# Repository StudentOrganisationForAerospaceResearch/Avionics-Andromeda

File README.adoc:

= Andromeda Sensor Development Board

Andromeda is the development board for SOAR's 2018 competition avionics system.

Hardware Designs are incremented by version.
For example; *AndromedaV1* is version 1.

The design files for each version are available along with pdf schematics,
assembly drawings and gerber files.

Each hardware version contains the following design files
----

* ___VX.pro - Kicad project
* ___VX.sch - Kicad main schematic
* ___VX.kicad_pcb - Kicad PCB design
* ___.sch - several hierarchical schematic
* ___V.net - Kicad netlist file
* ___VX-cache.dcm - Kicad component description cache
* ___VX-cache.lib - Kicad component library cache
* ___VX-Schematic.pdf - PDF Schematic
* ___VX-AssemblyDrawing.pdf PDF export of fabrication layer
* Gerbers - Gerber files exported with protel extensions
----

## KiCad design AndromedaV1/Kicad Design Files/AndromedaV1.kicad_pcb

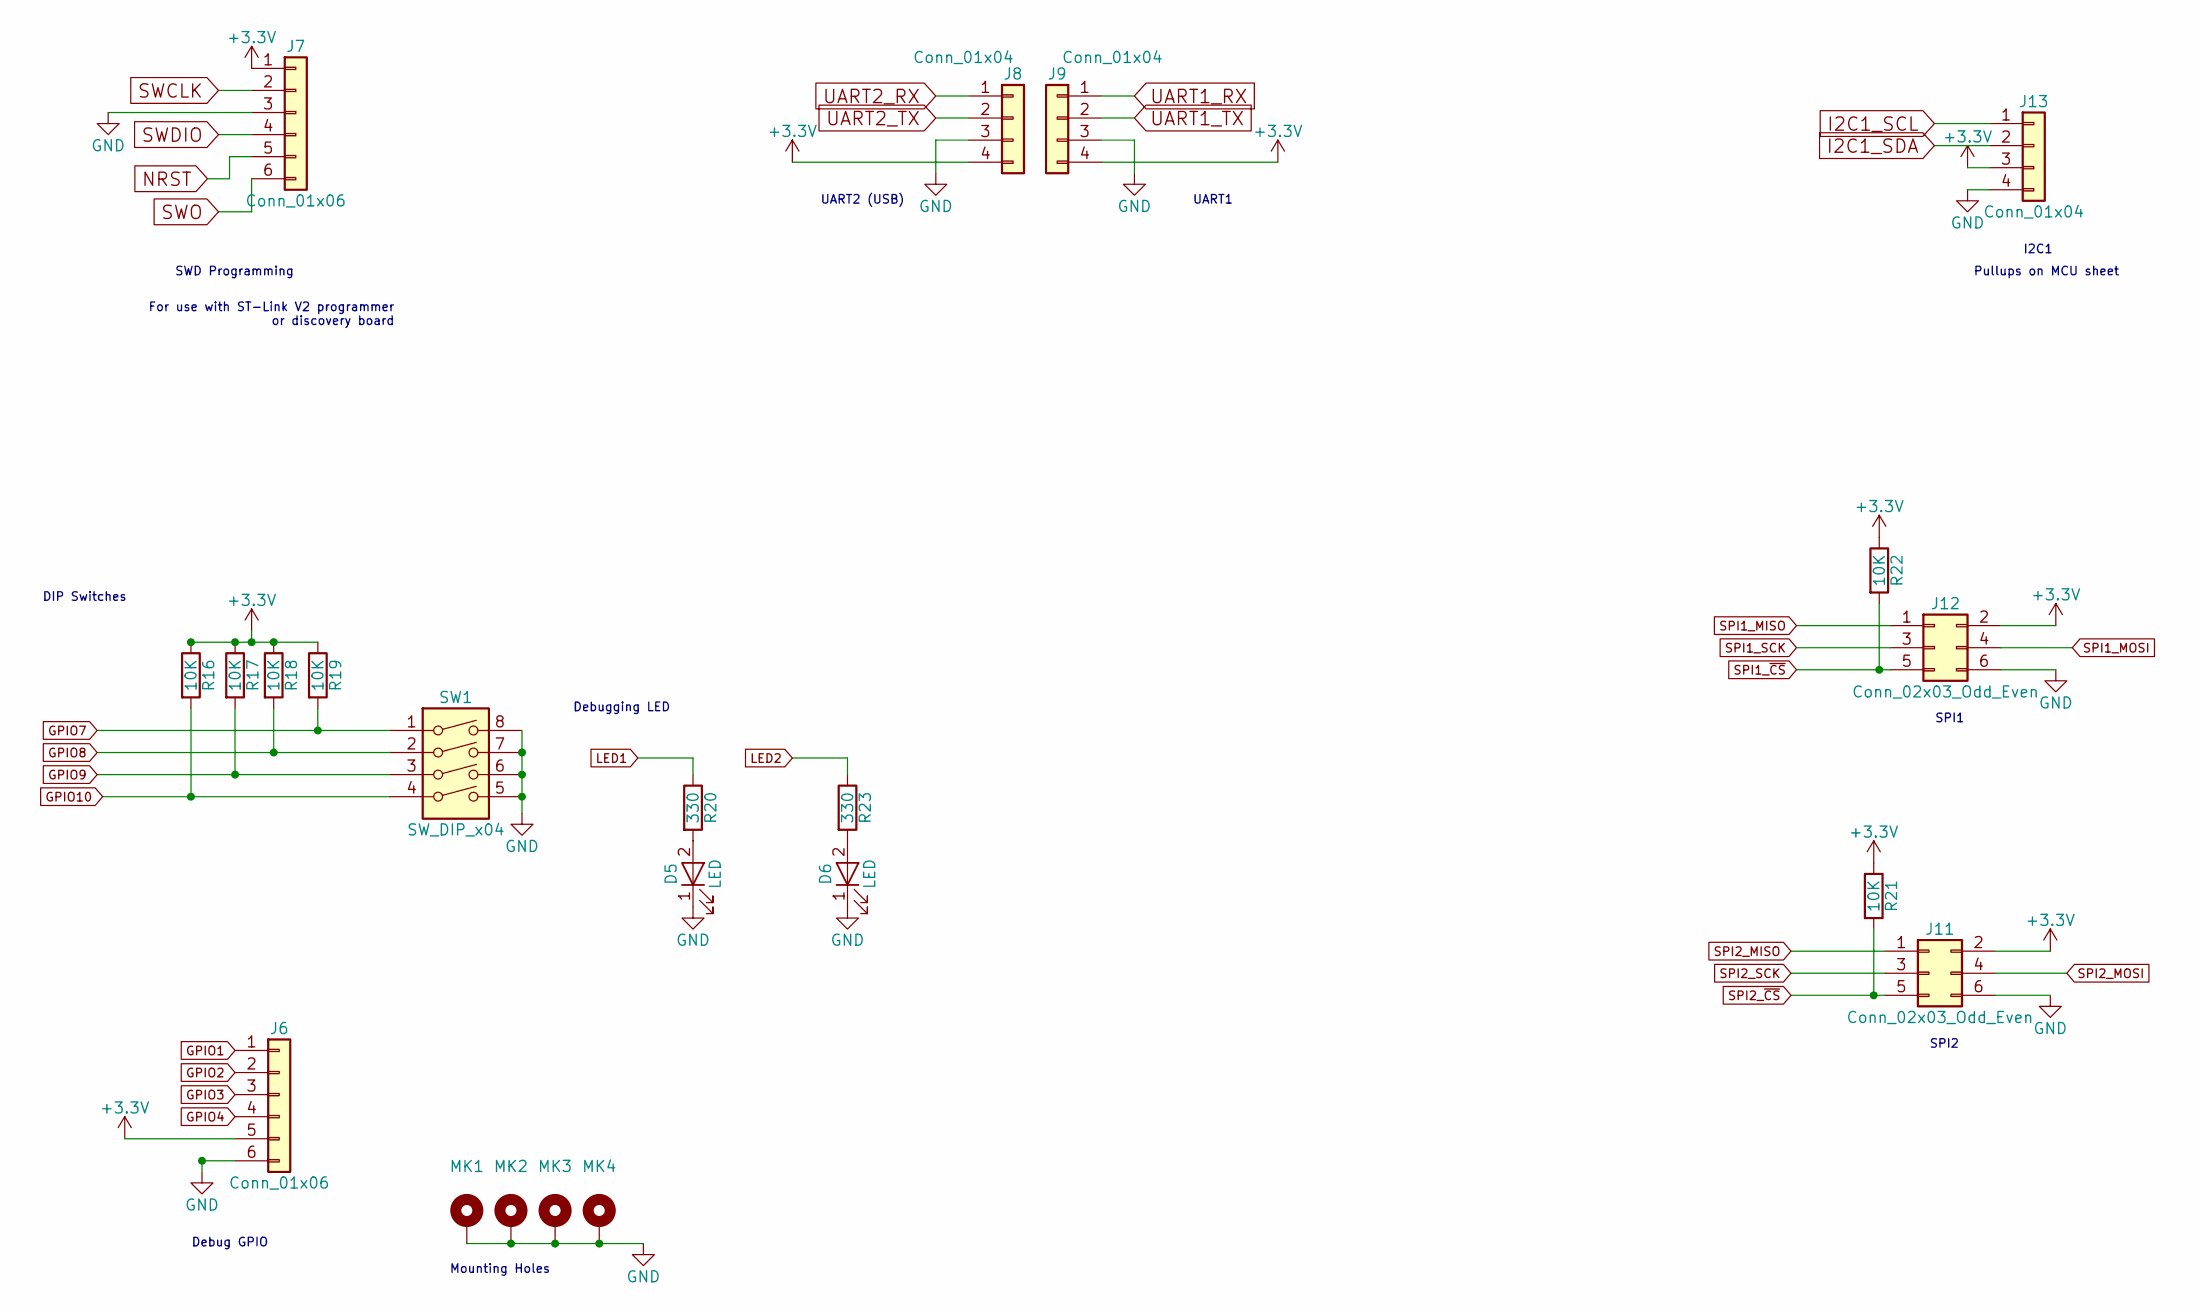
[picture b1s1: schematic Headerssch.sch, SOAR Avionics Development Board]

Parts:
D5, D6: LED; LED_0805_2012Metric
J6, J7: Conn_01x06; PinHeader_1x06_P2.54mm_Vertical
J8, J9, J13: Conn_01x04; PinHeader_1x04_P2.54mm_Vertical; Digikey 609-3262-ND
J11, J12: Conn_02x03_Odd_Even; PinHeader_2x03_P2.54mm_Vertical
MK1, MK2, MK3, MK4: Mounting_Hole_PAD; MountingHole_3.2mm_M3_Pad
R16, R17, R18, R19, R21, R22: 10K; R_0603_1608Metric
R20, R23: 330; R_0603_1608Metric
SW1: SW_DIP_x04; SW_DIP_x4_W8.61mm_Slide_LowProfile; Digikey CT2194MST-ND

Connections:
+3V3: J6.5, J7.1, J8.4, J9.4, J11.2, J12.2, J13.3, R16.1, R17.1, R18.1, R19.1, R21.1, R22.1; also elsewhere on the board
GND: D5.1 (K), D6.1 (K), J6.6, J7.3, J8.3, J9.3, J11.6, J12.6, J13.4, MK1.1, MK2.1, MK3.1, MK4.1, SW1.5, SW1.6, SW1.7, SW1.8; also elsewhere on the board
GPIO1: J6.1; also elsewhere on the board
GPIO2: J6.2; also elsewhere on the board
GPIO3: J6.3; also elsewhere on the board
GPIO4: J6.4; also elsewhere on the board
GPIO7: R19.2, SW1.1; also elsewhere on the board
GPIO8: R18.2, SW1.2; also elsewhere on the board
GPIO9: R17.2, SW1.3; also elsewhere on the board
GPIO10: R16.2, SW1.4; also elsewhere on the board
I2C1_SCL: J13.1; also elsewhere on the board
I2C1_SDA: J13.2; also elsewhere on the board
LED1: R20.1; also elsewhere on the board
LED2: R23.1; also elsewhere on the board
NRST: J7.5; also elsewhere on the board
unnamed: D5.2 (A), R20.2
unnamed: D6.2 (A), R23.2
SPI1_MISO: J12.1; also elsewhere on the board
SPI1_MOSI: J12.4; also elsewhere on the board
SPI1_SCK: J12.3; also elsewhere on the board
SPI1_~CS: J12.5, R22.2; also elsewhere on the board
SPI2_MISO: J11.1; also elsewhere on the board
SPI2_MOSI: J11.4; also elsewhere on the board
SPI2_SCK: J11.3; also elsewhere on the board
SPI2_~CS: J11.5, R21.2; also elsewhere on the board
SWCLK: J7.2; also elsewhere on the board
SWDIO: J7.4; also elsewhere on the board
SWO: J7.6; also elsewhere on the board
UART1_RX: J9.1; also elsewhere on the board
UART1_TX: J9.2; also elsewhere on the board
UART2_RX: J8.1; also elsewhere on the board
UART2_TX: J8.2; also elsewhere on the board

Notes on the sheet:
SWD Programming
UART2 (USB)
UART1
I2C1
SPI1
Debug GPIO
For use with ST-Link V2 programmer or discovery board
Debugging LED
SPI2
Pullups on MCU sheet
DIP Switches
Mounting Holes

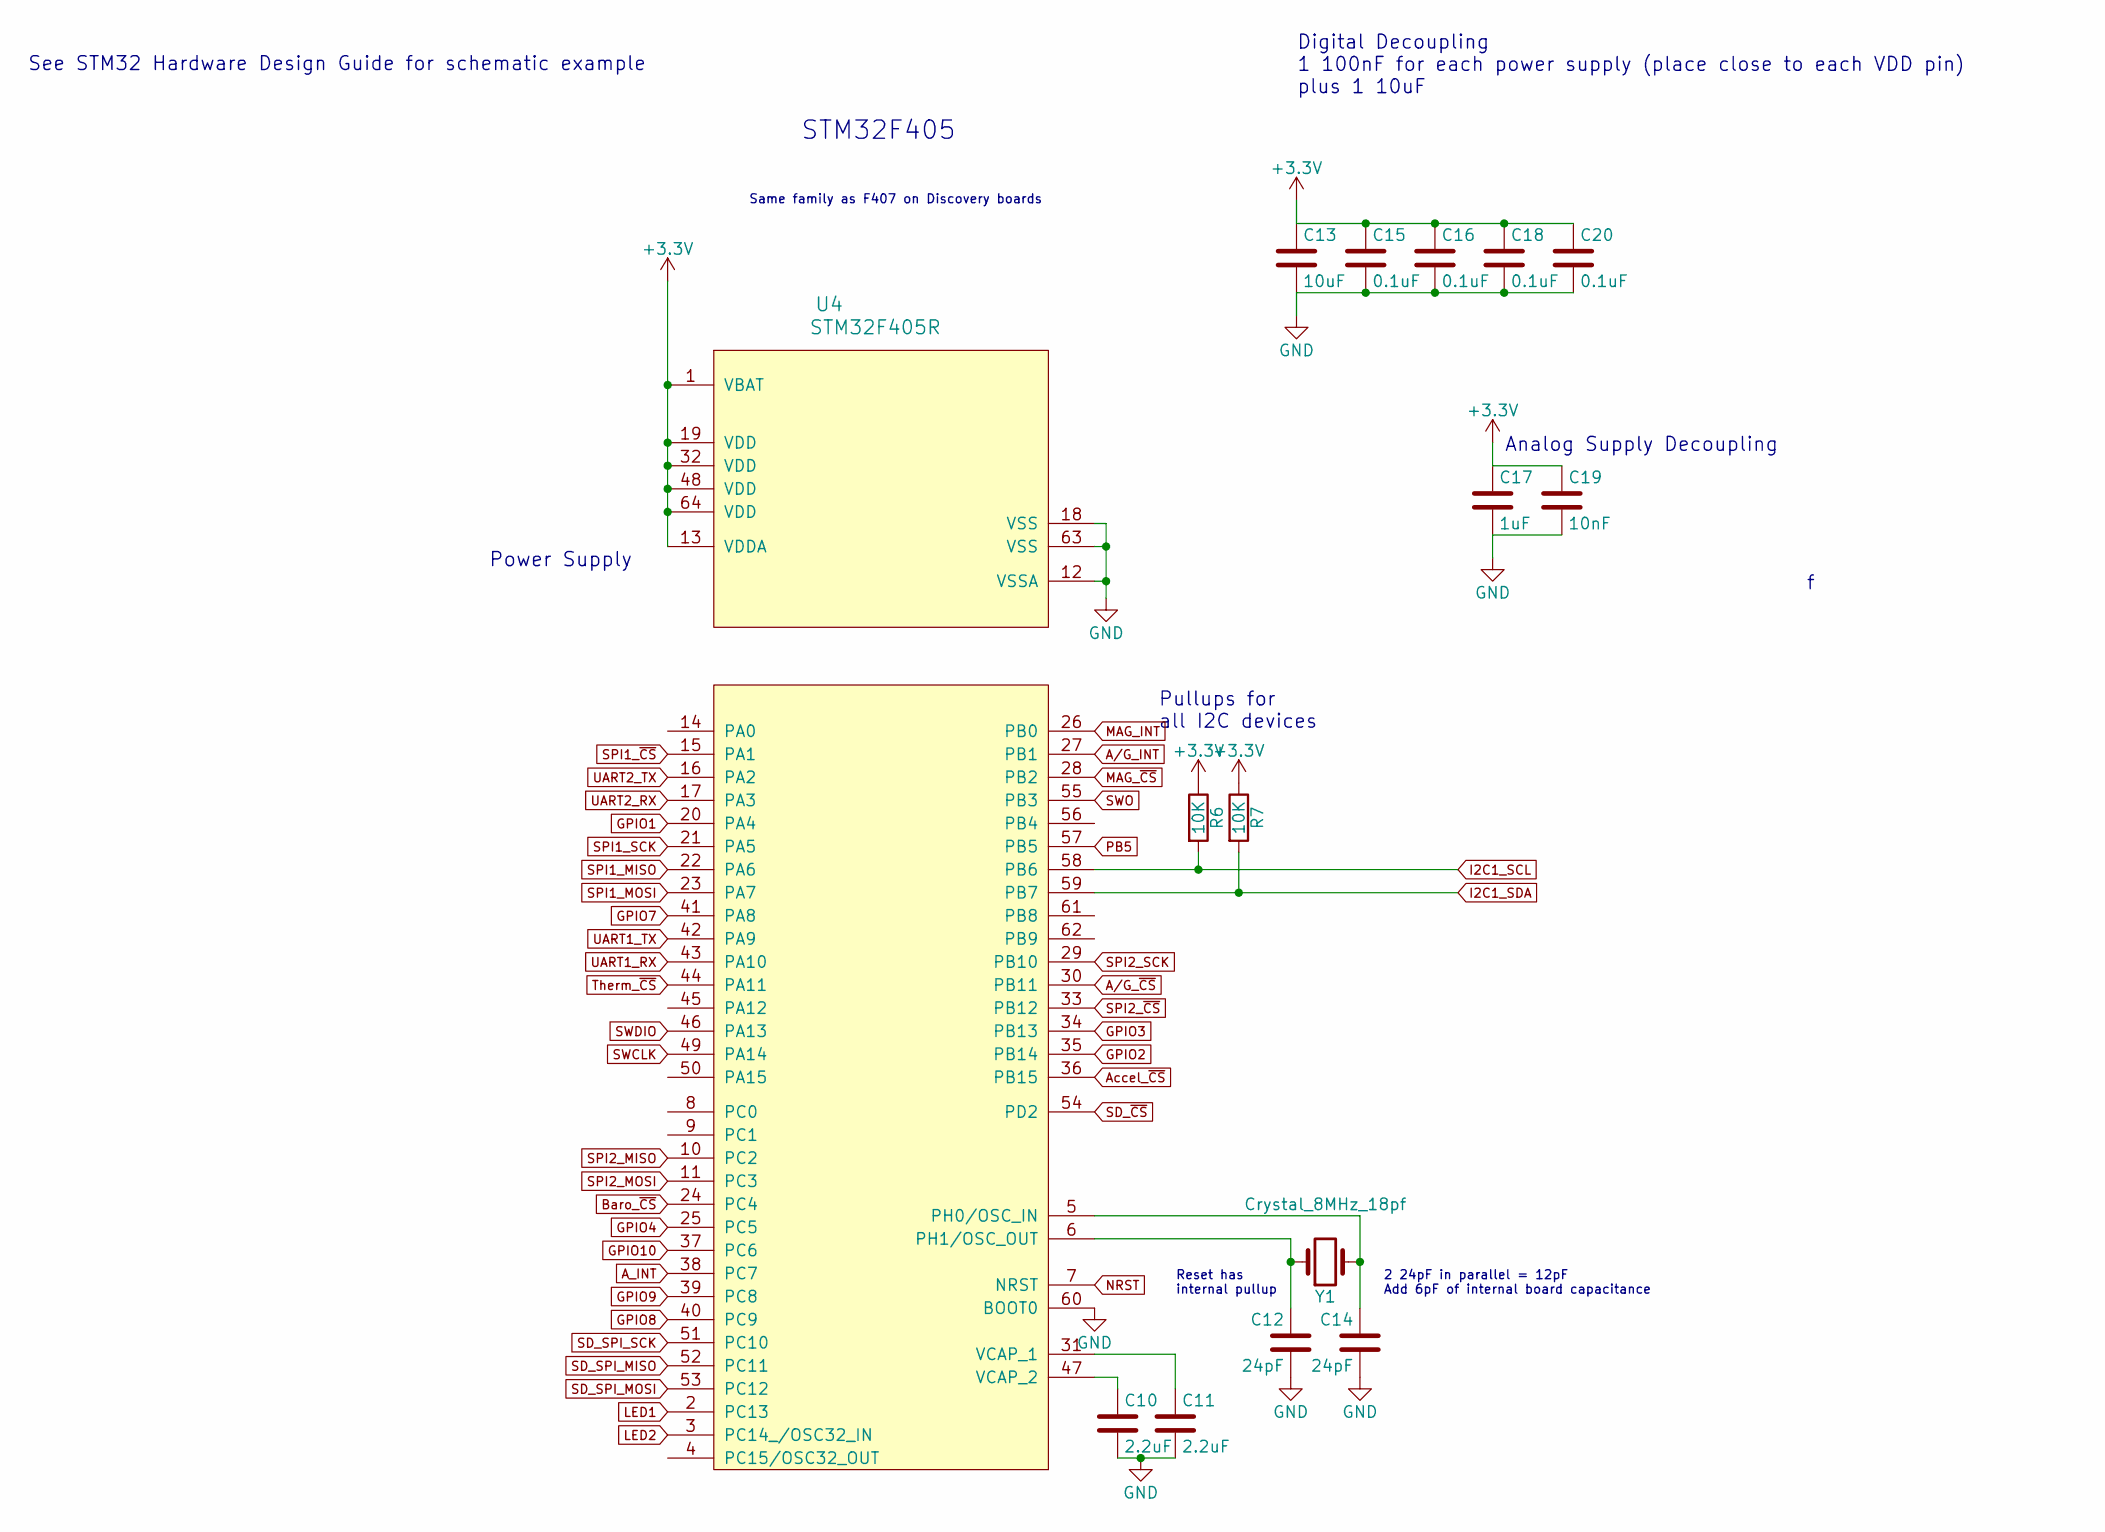
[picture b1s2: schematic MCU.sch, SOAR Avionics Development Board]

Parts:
C10, C11: 2.2uF; C_0603_1608Metric
C12, C14: 24pF; C_0603_1608Metric
C13: 10uF; C_0603_1608Metric
C15, C16, C18, C20: 0.1uF; C_0603_1608Metric
C17: 1uF; C_0603_1608Metric
C19: 10nF; C_0603_1608Metric
R6, R7: 10K; R_0603_1608Metric
U4: STM32F405R; LQFP-64_10x10mm_P0.5mm; Digikey 497-11767-ND
Y1: Crystal_8MHz_18pf; Crystal_SMD_SeikoEpson_MA505-2Pin_12.7x5.1mm; Digikey 535-9089-1-ND

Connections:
+3V3: C13.1, C15.1, C16.1, C17.1, C18.1, C19.1, C20.1, R6.1, R7.1, U4.1 (VBAT), U4.13 (VDDA), U4.19 (VDD), U4.32 (VDD), U4.48 (VDD), U4.64 (VDD); also elsewhere on the board
A/G_INT: U4.27 (PB1); also elsewhere on the board
A/G_~CS: U4.30 (PB11); also elsewhere on the board
A_INT: U4.38 (PC7); also elsewhere on the board
Accel_~CS: U4.36 (PB15); also elsewhere on the board
Baro_~CS: U4.24 (PC4); also elsewhere on the board
GND: C10.2, C11.2, C12.2, C13.2, C14.2, C15.2, C16.2, C17.2, C18.2, C19.2, C20.2, U4.12 (VSSA), U4.18 (VSS), U4.60 (BOOT0), U4.63 (VSS); also elsewhere on the board
GPIO1: U4.20 (PA4); also elsewhere on the board
GPIO2: U4.35 (PB14); also elsewhere on the board
GPIO3: U4.34 (PB13); also elsewhere on the board
GPIO4: U4.25 (PC5); also elsewhere on the board
GPIO7: U4.41 (PA8); also elsewhere on the board
GPIO8: U4.40 (PC9); also elsewhere on the board
GPIO9: U4.39 (PC8); also elsewhere on the board
GPIO10: U4.37 (PC6); also elsewhere on the board
I2C1_SCL: R6.2, U4.58 (PB6); also elsewhere on the board
I2C1_SDA: R7.2, U4.59 (PB7); also elsewhere on the board
LED1: U4.2 (PC13); also elsewhere on the board
LED2: U4.3 (PC14_/OSC32_IN); also elsewhere on the board
MAG_INT: U4.26 (PB0); also elsewhere on the board
MAG_~CS: U4.28 (PB2); also elsewhere on the board
NRST: U4.7 (NRST); also elsewhere on the board
unnamed: C10.1, U4.47 (VCAP_2)
unnamed: C11.1, U4.31 (VCAP_1)
unnamed: C12.1, U4.6 (PH1/OSC_OUT), Y1.1
unnamed: C14.1, U4.5 (PH0/OSC_IN), Y1.2
PB5: U4.57 (PB5)
SD_SPI_MISO: U4.52 (PC11); also elsewhere on the board
SD_SPI_MOSI: U4.53 (PC12); also elsewhere on the board
SD_SPI_SCK: U4.51 (PC10); also elsewhere on the board
SD_~CS: U4.54 (PD2); also elsewhere on the board
SPI1_MISO: U4.22 (PA6); also elsewhere on the board
SPI1_MOSI: U4.23 (PA7); also elsewhere on the board
SPI1_SCK: U4.21 (PA5); also elsewhere on the board
SPI1_~CS: U4.15 (PA1); also elsewhere on the board
SPI2_MISO: U4.10 (PC2); also elsewhere on the board
SPI2_MOSI: U4.11 (PC3); also elsewhere on the board
SPI2_SCK: U4.29 (PB10); also elsewhere on the board
SPI2_~CS: U4.33 (PB12); also elsewhere on the board
SWCLK: U4.49 (PA14); also elsewhere on the board
SWDIO: U4.46 (PA13); also elsewhere on the board
SWO: U4.55 (PB3); also elsewhere on the board
Therm_~CS: U4.44 (PA11); also elsewhere on the board
UART1_RX: U4.43 (PA10); also elsewhere on the board
UART1_TX: U4.42 (PA9); also elsewhere on the board
UART2_RX: U4.17 (PA3); also elsewhere on the board
UART2_TX: U4.16 (PA2); also elsewhere on the board

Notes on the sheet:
Reset has internal pullup
Digital Decoupling 1 100nF for each power supply (place close to each VDD pin) plus 1 10uF
Analog Supply Decoupling
Pullups for all I2C devices
See STM32 Hardware Design Guide for schematic example
Power Supply
2 24pF in parallel = 12pF Add 6pF of internal board capacitance
STM32F405
Same family as F407 on Discovery boards

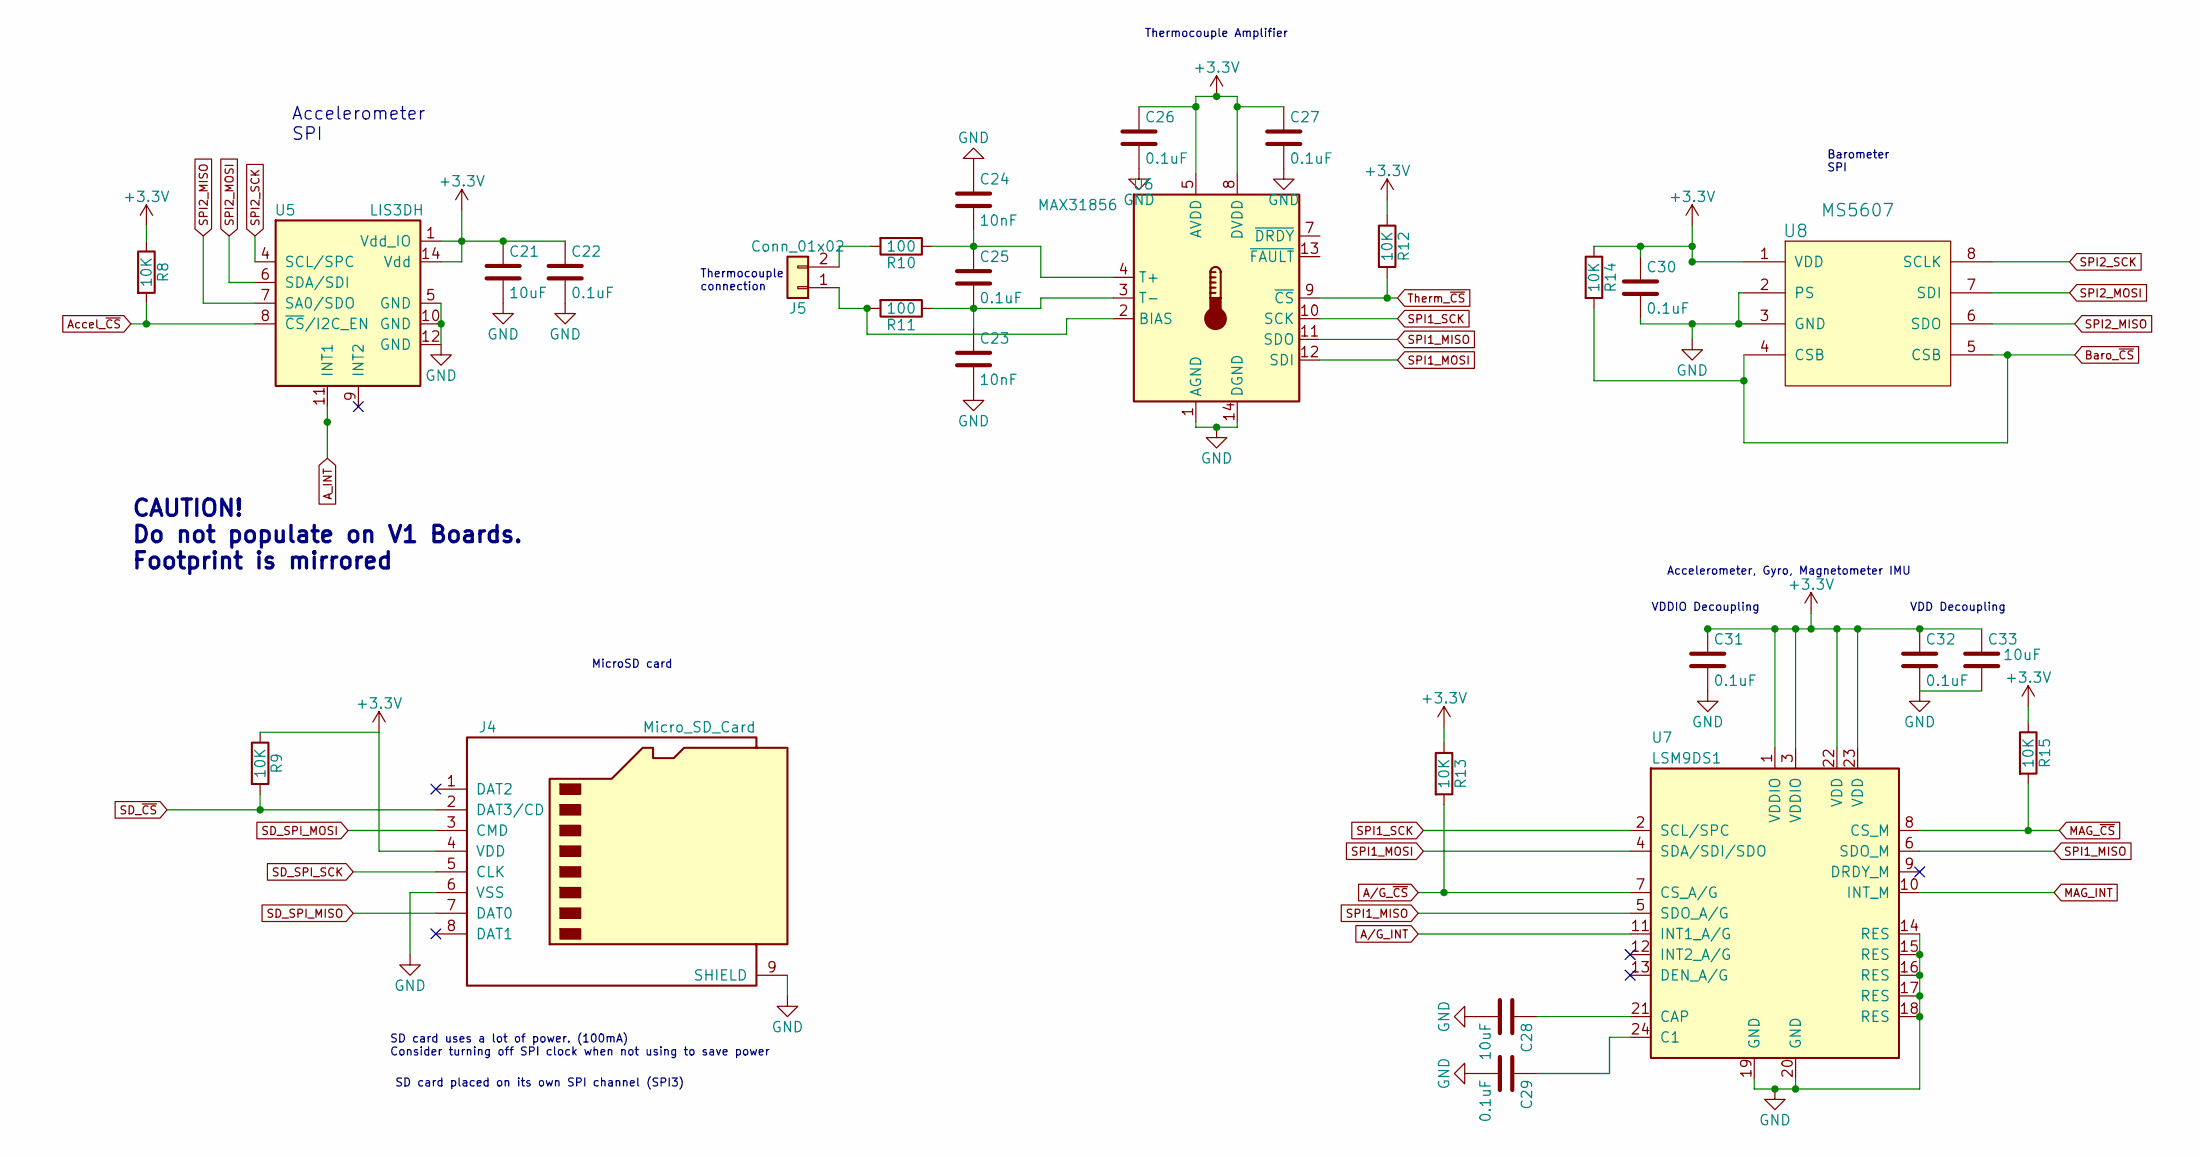
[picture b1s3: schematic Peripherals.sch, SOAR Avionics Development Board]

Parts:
C21, C28, C33: 10uF; C_0603_1608Metric
C22, C25, C26, C27, C29, C30, C31, C32: 0.1uF; C_0603_1608Metric
C23, C24: 10nF; C_0603_1608Metric
J4: Micro_SD_Card; Conn,Molex,Hinged_microSD; Digikey 0472192001
J5: Conn_01x02; PinHeader_1x02_P2.54mm_Vertical
R8, R9, R12, R13, R14, R15: 10K; R_0603_1608Metric
R10, R11: 100; R_0603_1608Metric
U5: LIS3DH; LGA-16
U6: MAX31856; TSSOP-14_4.4x5mm_P0.65mm; Digikey MAX31856MUD+-ND
U7: LSM9DS1; LGA-24L_3x3.5mm_P0.43mm; Digikey 497-14946-1-ND
U8: MS5607; LGA-8_3x5mm_P1.25mm; Digikey MS560702BA03-00

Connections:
+3V3: C21.1, C22.1, C26.1, C27.1, C30.1, C31.1, C32.1, C33.1, J4.4 (VDD), R8.1, R9.1, R12.1, R13.1, R14.1, R15.1, U5.1 (Vdd_IO), U5.14 (Vdd), U6.5 (AVDD), U6.8 (DVDD), U7.1 (VDDIO), U7.3 (VDDIO), U7.22 (VDD), U7.23 (VDD), U8.1 (VDD); also elsewhere on the board
A/G_INT: U7.11 (INT1_A/G); also elsewhere on the board
A/G_~CS: R13.2, U7.7 (CS_A/G); also elsewhere on the board
A_INT: U5.11 (INT1); also elsewhere on the board
Accel_~CS: R8.2, U5.8 (~CS~/I2C_EN); also elsewhere on the board
Baro_~CS: R14.2, U8.4 (CSB), U8.5 (CSB); also elsewhere on the board
GND: C21.2, C22.2, C23.2, C24.1, C26.2, C27.2, C28.2, C29.2, C30.2, C31.2, C32.2, C33.2, J4.6 (VSS), J4.9 (SHIELD), U5.5 (GND), U5.10 (GND), U5.12 (GND), U6.1 (AGND), U6.14 (DGND), U7.14 (RES), U7.15 (RES), U7.16 (RES), U7.17 (RES), U7.18 (RES), U7.19 (GND), U7.20 (GND), U8.2 (PS), U8.3 (GND); also elsewhere on the board
MAG_INT: U7.10 (INT_M); also elsewhere on the board
MAG_~CS: R15.2, U7.8 (CS_M); also elsewhere on the board
unnamed: C23.1, C25.2, R11.1, U6.3 (T-)
unnamed: C24.2, C25.1, R10.1, U6.4 (T+)
unnamed: C28.1, U7.21 (CAP)
unnamed: C29.1, U7.24 (C1)
unnamed: J5.1, R11.2, U6.2 (BIAS)
unnamed: J5.2, R10.2
SD_SPI_MISO: J4.7 (DAT0); also elsewhere on the board
SD_SPI_MOSI: J4.3 (CMD); also elsewhere on the board
SD_SPI_SCK: J4.5 (CLK); also elsewhere on the board
SD_~CS: J4.2 (DAT3/CD), R9.2; also elsewhere on the board
SPI1_MISO: U6.11 (SDO), U7.5 (SDO_A/G), U7.6 (SDO_M); also elsewhere on the board
SPI1_MOSI: U6.12 (SDI), U7.4 (SDA/SDI/SDO); also elsewhere on the board
SPI1_SCK: U6.10 (SCK), U7.2 (SCL/SPC); also elsewhere on the board
SPI2_MISO: U5.7 (SA0/SDO), U8.6 (SDO); also elsewhere on the board
SPI2_MOSI: U5.6 (SDA/SDI), U8.7 (SDI); also elsewhere on the board
SPI2_SCK: U5.4 (SCL/SPC), U8.8 (SCLK); also elsewhere on the board
Therm_~CS: R12.2, U6.9 (~CS); also elsewhere on the board

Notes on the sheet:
SD card uses a lot of power. (100mA) Consider turning off SPI clock when not using to save power
Accelerometer SPI
Barometer SPI
VDD Decoupling
VDDIO Decoupling
Thermocouple Amplifier
Thermocouple connection
MicroSD card
Accelerometer, Gyro, Magnetometer IMU
SD card placed on its own SPI channel (SPI3)
CAUTION! Do not populate on V1 Boards. Footprint is mirrored

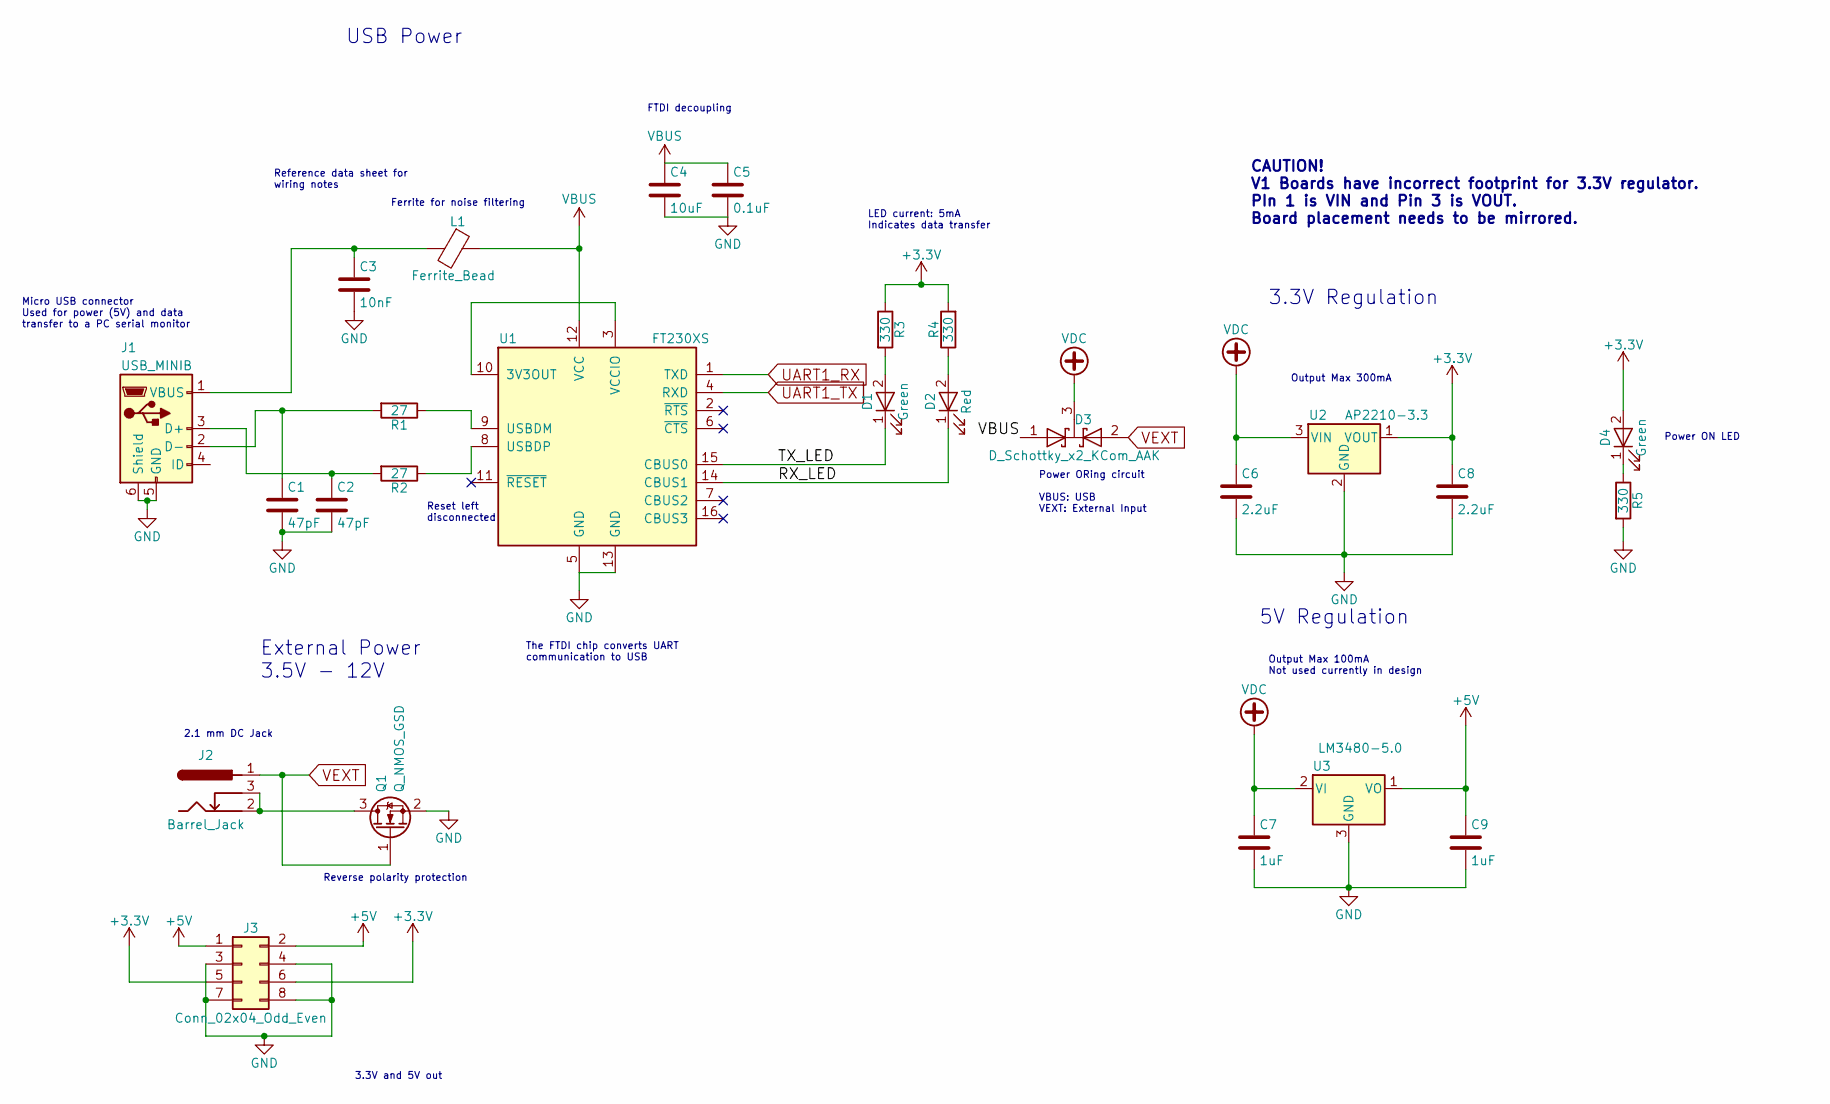
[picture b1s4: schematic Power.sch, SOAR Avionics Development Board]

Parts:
C1, C2: 47pF; C_0603_1608Metric
C3: 10nF; C_0603_1608Metric
C4: 10uF; C_0603_1608Metric
C5: 0.1uF; C_0603_1608Metric
C6, C8: 2.2uF; C_0603_1608Metric
C7, C9: 1uF; C_0603_1608Metric
D1, D4: Green; LED_0805_2012Metric; Digikey LG R971-KN-1
D2: Red; LED_0805_2012Metric; Digikey 475-1278-1-ND
D3: D_Schottky_x2_KCom_AAK; SOT-23; Digikey 1727-5188-1-ND
J1: USB_MINIB; USB-Mini-B; Digikey 690-005-299-043
J2: Barrel_Jack; CUI_PJ-102A; Digikey CP-102A-ND
J3: Conn_02x04_Odd_Even; PinHeader_2x04_P2.54mm_Vertical
L1: Ferrite_Bead; L_0603_1608Metric; Digikey 732-1593-1-ND
Q1: Q_NMOS_GSD; SOT-23; Digikey DMN3023L-7DICT-ND
R1, R2: 27; R_0603_1608Metric
R3, R4, R5: 330; R_0603_1608Metric
U1: FT230XS; SSOP-16_3.9x4.9mm_P0.635mm; Digikey 768-1135-1-ND
U2: AP2210-3.3; SOT-23; Digikey AP2210N-3.3TRG1
U3: LM3480-5.0; SOT-23; Digikey LM3480IM3X-5.0/NOPBCT-ND

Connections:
+3V3: C8.1, D4.2 (A), J3.5, J3.6, R3.1, R4.2, U2.1 (VOUT); also elsewhere on the board
+5V: C9.1, J3.1, J3.2, U3.1 (VO)
/Power and FTDI/RX_LED: D2.1 (K), U1.14 (CBUS1)
/Power and FTDI/TX_LED: D1.1 (K), U1.15 (CBUS0)
GND: C1.2, C2.2, C3.2, C4.2, C5.2, C6.2, C7.2, C8.2, C9.2, J1.5 (GND), J1.6 (Shield), J3.3, J3.4, J3.7, J3.8, Q1.2 (S), R5.2, U1.5 (GND), U1.13 (GND), U2.2 (GND), U3.3 (GND); also elsewhere on the board
unnamed: C1.1, J1.2 (D-), R1.2
unnamed: C2.1, J1.3 (D+), R2.2
unnamed: C3.1, J1.1 (VBUS), L1.2
unnamed: D1.2 (A), R3.2
unnamed: D2.2 (A), R4.1
unnamed: D4.1 (K), R5.1
unnamed: J2.2, J2.3, Q1.3 (D)
unnamed: R1.1, U1.9 (USBDM)
unnamed: R2.1, U1.8 (USBDP)
unnamed: U1.3 (VCCIO), U1.10 (3V3OUT)
UART1_RX: U1.1 (TXD); also elsewhere on the board
UART1_TX: U1.4 (RXD); also elsewhere on the board
VBUS: C4.1, C5.1, D3.1 (A), L1.1, U1.12 (VCC)
VDC: C6.1, C7.1, D3.3 (K), U2.3 (VIN), U3.2 (VI)
VEXT: D3.2 (A), J2.1, Q1.1 (G)

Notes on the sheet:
Reset left disconnected
Output Max 300mA
Power ON LED
LED current: 5mA Indicates data transfer
The FTDI chip converts UART communication to USB
Power ORing circuit VBUS: USB VEXT: External Input
Micro USB connector Used for power (5V) and data transfer to a PC serial monitor
Reference data sheet for wiring notes
Ferrite for noise filtering
FTDI decoupling
Reverse polarity protection
2.1 mm DC Jack
3.3V and 5V out
External Power 3.5V - 12V
USB Power
3.3V Regulation
Output Max 100mA Not used currently in design
5V Regulation
CAUTION! V1 Boards have incorrect footprint for 3.3V regulator. PIn 1 is VIN and Pin 3 is VOUT. Board placement needs to be mirrored.

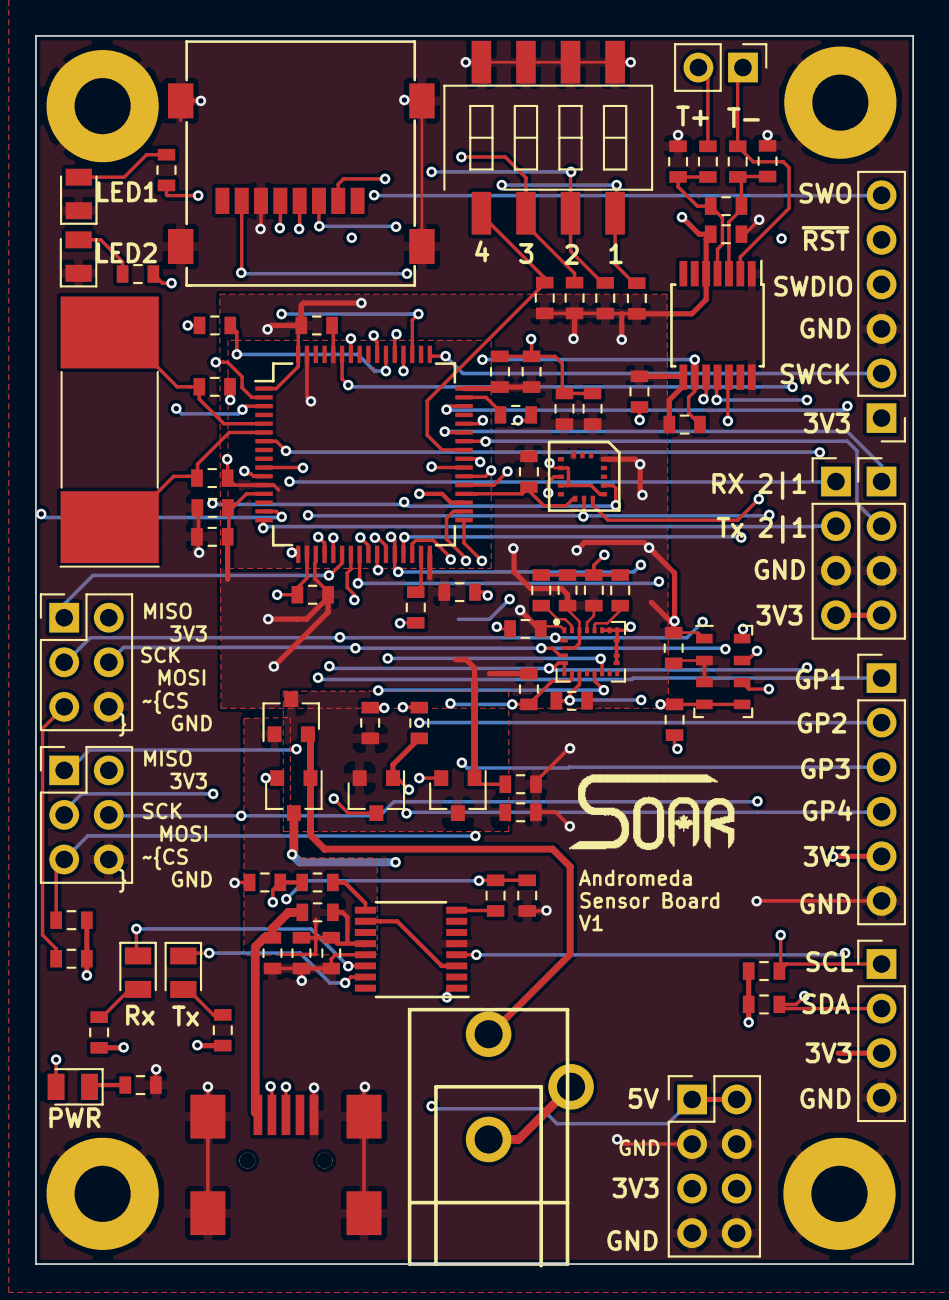
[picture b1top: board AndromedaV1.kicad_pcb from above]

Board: 4 copper layers, 50.0 x 70.0 mm, 91 parts (0 on the bottom side), 70 nets.

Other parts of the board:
LOGO_SOAR: LOGO_SOAR

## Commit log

2018-02-18 Initial commit of design files
2018-02-18 Restructure directories
